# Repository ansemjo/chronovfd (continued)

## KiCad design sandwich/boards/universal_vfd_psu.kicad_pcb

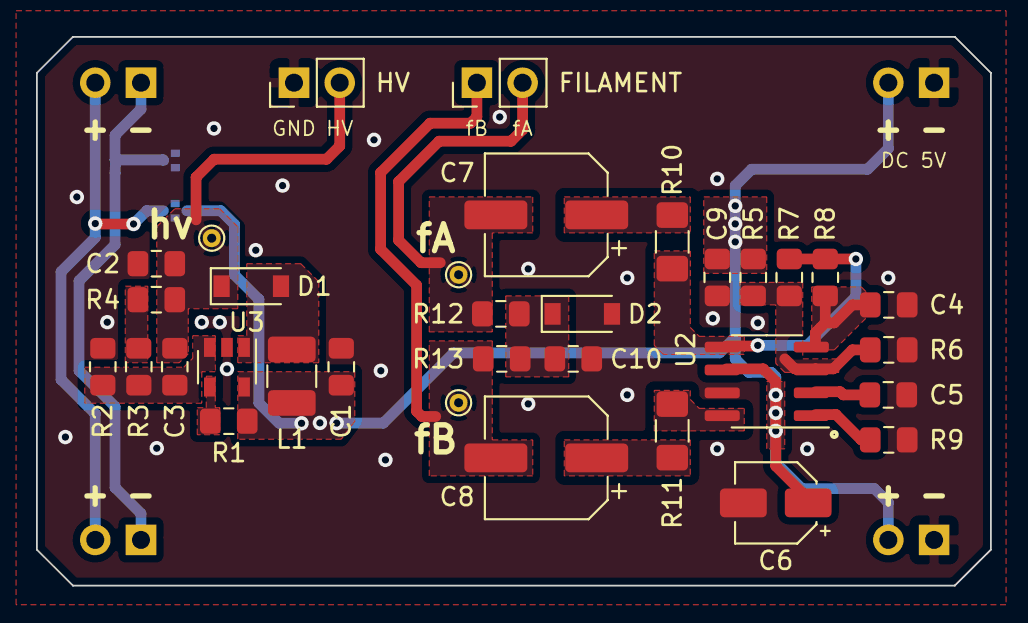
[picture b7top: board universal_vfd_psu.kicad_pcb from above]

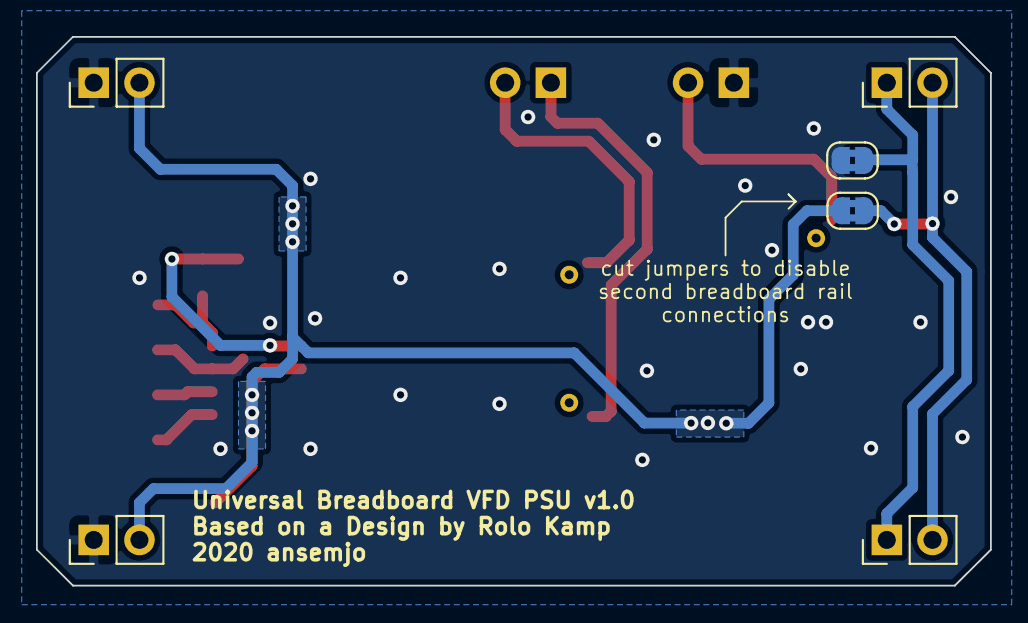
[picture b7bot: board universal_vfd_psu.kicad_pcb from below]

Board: 2 copper layers, 53.0 x 30.5 mm, 32 parts (2 on the bottom side), 18 nets.

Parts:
C1: 2.2µF; C_0805_2012Metric_Pad1.15x1.40mm_HandSolder
C2: 4.7µF; C_0805_2012Metric_Pad1.15x1.40mm_HandSolder
C3: 82pF; C_0805_2012Metric_Pad1.15x1.40mm_HandSolder
C4: 10nF; C_0805_2012Metric_Pad1.15x1.40mm_HandSolder
C5, C10: 1µF; C_0805_2012Metric_Pad1.15x1.40mm_HandSolder
C6: 10µF; CP_Elec_4x5.4
C7, C8: 47µF; CP_Elec_6.3x5.9
C9: 100nF; C_0805_2012Metric_Pad1.15x1.40mm_HandSolder
D1: 1N5819HW-7-F; D_SOD-123
D2: 3.3V; D_SOD-123
FILAMENT: PinHeader_1x02_P2.54mm_Vertical
GND: SolderJumper-2_P1.3mm_Bridged2Bar_RoundedPad1.0x1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; SolderJumper-2_P1.3mm_Bridged2Bar_RoundedPad1.0x1.5mm
HV: PinHeader_1x02_P2.54mm_Vertical
L1: 10µH; L_1210_3225Metric_Pad1.42x2.65mm_HandSolder
R1: 47kΩ; R_0805_2012Metric_Pad1.15x1.40mm_HandSolder
R2: 13kΩ; R_0805_2012Metric_Pad1.15x1.40mm_HandSolder
R3: 240kΩ; R_0805_2012Metric_Pad1.15x1.40mm_HandSolder
R4, R5, R6, R7, R9: 10kΩ; R_0805_2012Metric_Pad1.15x1.40mm_HandSolder
R8: 2.2kΩ; R_0805_2012Metric_Pad1.15x1.40mm_HandSolder
R10, R11: 10Ω; R_1206_3216Metric_Pad1.42x1.75mm_HandSolder
R12, R13: 220Ω; R_0805_2012Metric_Pad1.15x1.40mm_HandSolder
U2: LM4871MX_NOPB; SOIC-8_3.9x4.9mm_P1.27mm
U3: LM2733YMF; SOT-23-5
VCC: SolderJumper-2_P1.3mm_Bridged2Bar_RoundedPad1.0x1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; SolderJumper-2_P1.3mm_Bridged2Bar_RoundedPad1.0x1.5mm

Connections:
/5V: C1.1, C6.1, C9.1, L1.1, R1.1, R5.1, U2.6, U3.5, VCC.2
/FIL_A: C7.2, FILAMENT.2, R12.2
/FIL_B: C8.2, FILAMENT.1, R13.2
/FIL_SHDN: R9.1, U2.1
/HV: C2.1, C3.2, D1.1, HV.2, R4.1
/~HV_SHDN~: R1.2, U3.4
GND: C1.2, C2.2, C4.2, C5.2, C6.2, C9.2, C10.2, D2.2, GND.2, HV.1, R2.1, R6.2, R9.2, U2.7, U3.2
unnamed: C3.1, R2.2, R3.2, U3.3
unnamed: C4.1, R8.1, U2.4
unnamed: C5.1, U2.2
unnamed: C7.1, R10.1
unnamed: C8.1, R11.1
unnamed: C10.1, D2.1, R12.1, R13.1
unnamed: D1.2, L1.2, U3.1
unnamed: R3.1, R4.2
unnamed: R5.2, R6.1, R7.2, U2.3
unnamed: R7.1, R8.2, R10.2, U2.5
unnamed: R11.2, U2.8

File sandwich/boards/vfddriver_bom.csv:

References,Value,Quantity Per PCB,Part,Digi-Key PN,MPN,Mfg
C9,100nF,1,C_Small,1276-1099-1-ND,CL21B104KACNNNC,Samsung
C4,10nF,1,C_Small,311-1136-1-ND,CC0805KRX7R9BB103,Yageo
C6,10µF,1,CP_Small,493-2100-1-ND,UWX1C100MCL1GB,Nichicon
C5 C10,1µF,2,C_Small,1276-6469-1-ND,CL21B105KAFNNNG,Samsung
C1 C2,4.7µF,2,C_Small,587-5485-1-ND,UMK212BBJ475KG-T,Taiyo Yuden
C7 C8,47µF,2,CP_Small,493-6385-1-ND,UCD1E470MCL1GS,Nichicon
C3,82pF,1,C_Small,311-1110-1-ND,CC0805JRNPO9BN820,Yageo
D1,1N5819HW-7-F,1,1N5819,1N5819HW-FDICT-ND,1N5819HW-7-F,Diodes Inc.
D2,3.3V,1,D_Zener_Small,MMSZ4684T1GOSCT-ND,MMSZ4684T1G,ON Semi
J1,Connection Header,1,Conn_01x08_Male,S2112EC-40-ND,PREC040DBAN-M71RC,Sullins
L1,10µH,1,L_Small,587-6332-1-ND,LBC3225T100MR,Taiyo Yuden
R4 R5 R6 R7 R9,10kΩ,5,R_Small,311-10.0KCRCT-ND,RC0805FR-0710KL,Yageo
R10 R11,12Ω 0.25W,2,R_Small,311-10.0FRCT-ND,RC1206FR-0710RL,Yageo
R2,13kΩ,1,R_Small,311-13.0KCRCT-ND,RC0805FR-0713KL,Yageo
R8,2.2kΩ,1,R_Small,311-2.20KCRCT-ND,RC0805FR-072K2L,Yageo
R12 R13,220Ω,2,R_Small,311-220CRCT-ND,RC0805FR-07220RL,Yageo
R3,240kΩ,1,R_Small,311-240KCRCT-ND,RC0805FR-07240KL,Yageo
R1 R14,47kΩ,2,R_Small,311-47.0KCRCT-ND,RC0805FR-0747KL,Yageo
U4,HV5812WG,1,HV5812WG,HV5812WG-GCT-ND,HV5812WG-G,Microchip
U1,IVL2-5_7,1,IVL2-5_7,,IVL2-7/5,
U3,LM2733YMF,1,LM2733YMF,LM2733YMF/NOPBCT-ND,LM2733YMF/NOPB,Texas Instr
U2,LM4871MX_NOPB,1,LM4871MX_NOPB,LM4871MX/NOPBCT-ND,LM4871MX/NOPB,Texas Instr

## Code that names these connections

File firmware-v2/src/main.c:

#include <avr/io.h>
#include <avr/interrupt.h>
#include <util/delay.h>
#include <assert.h>

#include "segments.h"
#include "i2c_peripheral.h"

// filament pins
#define filFWD  PIN2_bm // PB2
#define filREV  PIN3_bm // PB3
#define filVREF PIN6_bm // PA6

// hv5812 pins
#define hvDATA   PIN1_bm // PA1
#define hvCLOCK  PIN3_bm // PA3
#define hvSTROBE PIN4_bm // PA4

// setup the main cpu clock control to run at full speed
void init_cpufrequency() {
  //! check that fuse 0x02 OSCCFG has set FREQSEL = 0x02 to run at 20MHz
  assert((0b11 & FUSE_OSCCFG) == FREQSEL_20MHZ_gc);
  assert(F_CPU == 20000000L);
  _PROTECTED_WRITE(CLKCTRL.MCLKCTRLA, CLKCTRL_CLKSEL_OSC20M_gc); // select internal oscillator
  _PROTECTED_WRITE(CLKCTRL.MCLKCTRLB, (0 << CLKCTRL_PEN_bp));    // disable prescaler for full 20 MHz
}

// setup output pins to filament driver
void init_filament(uint8_t dac_data) {
  // setup output pins
  PORTA.DIRSET = filVREF;         // setup vref pin as output
  PORTA.OUTCLR = filVREF;         // start with reference voltage low
  PORTB.DIRSET = filFWD | filREV; // setup direction pins as outputs
  PORTB.OUTSET = filFWD;          // set one direction pin high
  // setup dac for vref pin
  DAC0.DATA  = dac_data;                           // write specified value
  register8_t vref = (VREF.CTRLA & ~(0b00000111)); // read & mask the current ctrla setting
  VREF.CTRLA = vref | VREF_DAC0REFSEL_2V5_gc;      // select internal 2.5 V voltage reference for dac
  DAC0.CTRLA = DAC_ENABLE_bm | DAC_OUTEN_bm;       // enable dac and output to PA6
}

// send data to the shift register and latch to vfd outputs
void display(uint16_t data) {
  PORTA.OUTCLR = hvSTROBE;
  while (!(SPI0.INTFLAGS & SPI_DREIF_bm)) { ; }
  SPI0.DATA = 0xFF & (data >> 8);
  while (!(SPI0.INTFLAGS & SPI_DREIF_bm)) { ; }
  SPI0.DATA = 0xFF & (data);
  while (!(SPI0.INTFLAGS & SPI_TXCIF_bm)) { ; }
  SPI0.INTFLAGS |= SPI_TXCIF_bm;
  PORTA.OUTSET = hvSTROBE;
  asm volatile("nop");
  PORTA.OUTCLR = hvSTROBE;
}

// setup spi controller to communicate with hv5812 shift register
void init_hv5812() {
  PORTA.DIRSET = hvDATA | hvCLOCK | hvSTROBE;  // setup pins to hv5812 as outputs
  PORTA.OUTCLR = hvDATA | hvCLOCK | hvSTROBE;  // set all pins low explicitly
  SPI0.CTRLA  = SPI_PRESC_DIV4_gc;             // set spi prescaler to result in ca. 5 MHz clock
  SPI0.CTRLA |= SPI_MASTER_bm | SPI_ENABLE_bm; // enable spi in controller mode
  SPI0.CTRLB  = SPI_BUFEN_bm | SPI_SSD_bm;     // double-buffered mode, don't use chip select
  display(0);                                  // all segments and grids off initially
}


volatile int digit = 0;
uint16_t digits[] = {
  G1 | Aa|Ad|Ae|Af|Ag, // E
  G2 | Ab|Ac|Ae|Af|Ag, // H
  G4 | Ad|Ae|Af, // L
  G5 | Aa|Ab|Ac|Ad|Ae|Af, // O
};
#define DIGITS (sizeof(digits)/sizeof(uint16_t))

// periodic interrupt service routing for digit time-multiplexing
ISR(RTC_PIT_vect) {
  RTC.PITINTFLAGS = RTC_PI_bm;    // clear interrupt flag
  display(digits[digit]);         // display next digit
  digit = (digit+1) % DIGITS;     // increment digit position
  PORTB.OUTTGL = filFWD | filREV; // toggle filament drive direction // TODO
}

// setup the periodic interrupt timer for digit time-multiplexing
void init_digit_multiplexing() {
  RTC.CLKSEL = RTC_CLKSEL_INT32K_gc;                 // use internal 32kHz
  RTC.PITINTCTRL = RTC_PI_bm;                        // enable periodic interrupt
  RTC.PITCTRLA = RTC_PERIOD_CYC32_gc | RTC_PITEN_bm; // enable PIT with 1 msec period
  sei();
}

// setup the adc to measure the photodiode current, i.e. ambient brightness
void init_photodiode_adc() {
  PORTA.DIRCLR = PIN7_bm;                                 // PA7 input
  PORTA.PIN7CTRL = PORT_ISC_INPUT_DISABLE_gc;             // disable input buffer
  register8_t vref = (VREF.CTRLA & ~(0b01110000));        // read & mask the current ctrla setting
  VREF.CTRLA = vref | VREF_ADC0REFSEL_0V55_gc;            // select internal 0.55 V voltage reference for adc
  ADC0.CTRLC = ADC_REFSEL_INTREF_gc | ADC_PRESC_DIV64_gc  // compate with internal reference, /64 prescaler
    | ADC_SAMPCAP_bm;                                     // use the smaller sampling capacitance
  ADC0.CTRLD = ADC_INITDLY_DLY32_gc | ADC_ASDV_ASVON_gc;  // some sample delay and randomization
  ADC0.SAMPCTRL = 0x1F;                                   // longer sampling time for high-impedance input
  ADC0.MUXPOS = ADC_MUXPOS_AIN7_gc;                       // sample on PA7 input
  ADC0.CTRLA |= ADC_ENABLE_bm;                            // enable
  ADC0.COMMAND = ADC_STCONV_bm;                           // start first conversion right away
}

// simple moving average over last few measurements
uint16_t samples[] = { 0, 0, 0, 0, 0, 0, 0, 0, 0, 0, 0, 0, 0, 0, 0, 0 };
unsigned idx = 0;
unsigned sum = 0;
#define SAMPLES (sizeof(samples)/sizeof(samples[0]))

// sample the photodiode adc and return averaged value
uint16_t measure_photodiode() {
  ADC0.COMMAND = ADC_STCONV_bm; // start conversion
  while (ADC0.COMMAND & ADC_STCONV_bm); // wait
  uint16_t sample = ADC0.RES;
  sum -= samples[idx];
  samples[idx] = sample;
  sum += samples[idx];
  idx = (idx+1) % SAMPLES;
  return sum / SAMPLES;
}

// infinite loop with random noise
void noise() {
  const int delay = 30;
  while (1) {
    digits[0] = G1 | (SEGMENTMASK & rand());
    digits[1] = G2 | (SEGMENTMASK & rand());
    digits[2] = G4 | (SEGMENTMASK & rand());
    digits[3] = G5 | (SEGMENTMASK & rand());
    _delay_ms(delay);
  }
}

// continiously sample the ambient brightness and display the value
void adcdisplay() {
  init_photodiode_adc();
  const uint16_t masks[] = { G1, G2, G4, G5 };
  uint16_t measure;
  while (1) {
    measure = measure_photodiode();
    digits[0] = masks[0] | segment_lookup((measure/1000) % 10);
    digits[1] = masks[1] | segment_lookup((measure/100 ) % 10);
    digits[2] = masks[2] | segment_lookup((measure/10  ) % 10);
    digits[3] = masks[3] | segment_lookup((measure/1   ) % 10);
    _delay_ms(100);
  }
}

volatile uint8_t i2c_data[4] = { 0, 0, 0, 0 };

// setup as i2c peripheral
init_i2c_peripheral() {

  i2c_peripheral_init(0x68);
  sei();

  while (1) {
    digits[0] = G1 | segment_lookup(i2c_data[0]);
    digits[1] = G2 | segment_lookup(i2c_data[1]);
    digits[2] = G4 | segment_lookup(i2c_data[2]);
    digits[3] = G5 | segment_lookup(i2c_data[3]);
    _delay_ms(100);
  }

}

/* i2c wishlist:
 * (https://github.com/sparkfun/Serial7SegmentDisplay/wiki/Special-Commands#decimal)
 *   clear display
 *   colon on/off (cursor control)
 *   begin every write left and then loop aroung with every fourth byte
 *   brightness control
 *   set specific digit
 *   raw data entry escape
 *   address config
 *   factory reset ?!
 *   store configuration in eeprom
 */

void main(void) {

  init_cpufrequency();
  init_filament(200);
  init_hv5812();
  init_digit_multiplexing();

  // show EHLO at beginning
  digits[0] = G1 | segment_lookup('E');
  digits[1] = G2 | segment_lookup('H');
  digits[2] = G4 | segment_lookup('L');
  digits[3] = G5 | segment_lookup('O');
  _delay_ms(600);

  // noise();
  //adcdisplay();
  init_i2c_peripheral();

}

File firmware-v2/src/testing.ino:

#define FIL_FWD 5
#define FIL_REV 4
#define FIL_REF 2

#define HV_DATA   8
#define HV_CLOCK  10
#define HV_STROBE 0

void initpin(int pin, int state) {
  pinMode(pin, OUTPUT);
  digitalWrite(pin, state);
}

void toggle(int pin) {
  digitalWrite(pin, !digitalRead(pin));
}

void setup() {

  // setup pins for filament driver
  initpin(FIL_FWD, LOW);  // forward
  initpin(FIL_REV, HIGH);  // reverse
  initpin(FIL_REF, LOW); // reference

  // turn on filament
  VREF.CTRLA = 0x03; // set reference voltage to 4.3V
  analogWrite(FIL_REF, 100);

  // setup hv pins
  initpin(HV_DATA, LOW);
  initpin(HV_CLOCK, LOW);
  initpin(HV_STROBE, LOW);

  delay(100);

  // turn on all segments
  digitalWrite(HV_STROBE, LOW);
  shiftOut(HV_DATA, HV_CLOCK, MSBFIRST, 0xff);
  shiftOut(HV_DATA, HV_CLOCK, MSBFIRST, 0xff);
  digitalWrite(HV_STROBE, HIGH);

  delay(1000);

}

#define SEGMENTS 0x1dda
#define Aa 0x0c12
#define An 0x0c02
#define At 0x0c90
#define G1 0x2000
#define G2 0x0001
#define G3 0x0004
#define G4 0x0020
#define G5 0x0200

void filwait() {
  for (int i = 0; i < 3; i++) {
    toggle(FIL_FWD);
    toggle(FIL_REV);
    delay(1);
  }
}

void out(uint16_t data) {
  digitalWrite(HV_STROBE, LOW);
  shiftOut(HV_DATA, HV_CLOCK, MSBFIRST, 0xff & (data >> 8));
  shiftOut(HV_DATA, HV_CLOCK, MSBFIRST, 0xff & (data >> 0));
  digitalWrite(HV_STROBE, HIGH);
}

void loop() {

  filwait();
  out(Aa | G1);
  filwait();
  out(An | G2);
  filwait();
  out(At | G4);
  filwait();
  out(An | G5);

}

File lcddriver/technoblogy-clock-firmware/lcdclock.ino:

/* Low-Power LCD Clock

   David Johnson-Davies - www.technoblogy.com - 4th May 2021
   AVR128DA48 @ 24 MHz (internal oscillator; BOD disabled)
   
   CC BY 4.0
   Licensed under a Creative Commons Attribution 4.0 International license: 
   http://creativecommons.org/licenses/by/4.0/
*/

#include <avr/io.h>
#include <avr/interrupt.h>
#include <avr/sleep.h>

// Seven segment definitions

const int CharLen = 15;
uint8_t Char[CharLen] = {
//  abcdefg  Segments
  0b1111110, // 0
  0b0110000, // 1
  0b1101101, // 2
  0b1111001, // 3
  0b0110011, // 4
  0b1011011, // 5
  0b1011111, // 6
  0b1110000, // 7
  0b1111111, // 8
  0b1111011, // 9
  0b0000000, // 10  Space
  0b0000001, // 11  '-'
  0b1100011, // 12  Degree
  0b1001110, // 13  'C'
  0b0111110  // 14  'V'
};

const int Space = 10;
const int Minus = 11;
const int Degree = 12;
const int Celsius = 13;
const int Vee = 14;

// Ports **********************************************

PORT_t *Digit[4] = { &PORTD, &PORTC, &PORTA, &PORTB };

void PortSetup () {
  for (int p=0; p<4; p++) Digit[p]->DIR = 0xFF;       // All pins outputs
  PORTE.DIR = PIN0_bm;                      // COMs outputs, PE0 and PE1
  PORTF.DIR = PIN5_bm | PIN4_bm;                      // 1A, colon
}

// Real-Time Clock **********************************************

void RTCSetup () {
  uint8_t temp;
  // Initialize 32.768kHz Oscillator:

  // Disable oscillator:
  temp = CLKCTRL.XOSC32KCTRLA & ~CLKCTRL_ENABLE_bm;

  // Enable writing to protected register
  CPU_CCP = CCP_IOREG_gc;
  CLKCTRL.XOSC32KCTRLA = temp;

  while (CLKCTRL.MCLKSTATUS & CLKCTRL_XOSC32KS_bm);   // Wait until XOSC32KS is 0
  
  temp = CLKCTRL.XOSC32KCTRLA | CLKCTRL_LPMODE_bm;      // Use External Crystal & low power
  
  // Enable writing to protected register
  CPU_CCP = CCP_IOREG_gc;
  CLKCTRL.XOSC32KCTRLA = temp;
  
  temp = CLKCTRL.XOSC32KCTRLA | CLKCTRL_ENABLE_bm;    // Enable oscillator
  
  // Enable writing to protected register
  CPU_CCP = CCP_IOREG_gc;
  CLKCTRL.XOSC32KCTRLA = temp;
  
  // Initialize RTC
  while (RTC.STATUS > 0);                             // Wait until registers synchronized

  // 32.768kHz External Crystal Oscillator (XOSC32K)
  RTC.CLKSEL = RTC_CLKSEL_XOSC32K_gc;

  RTC.PITINTCTRL = RTC_PI_bm;                         // Periodic Interrupt: enabled
  
  // RTC Clock Cycles 512, enabled ie 64Hz interrupt
  RTC.PITCTRLA = RTC_PERIOD_CYC512_gc | RTC_PITEN_bm;
}

// Display Time **********************************************

void DisplayTime (unsigned long halfsecs) {
  uint8_t minutes = (halfsecs / 120) % 60;
  #ifdef TWELVEHOUR
  uint8_t hours = (halfsecs / 7200) % 12 + 1;
  #else
  uint8_t hours = (halfsecs / 7200) % 24;
  #endif
  Digit[0]->OUT = Char[hours/10];
  Digit[1]->OUT = Char[hours%10];
  Digit[2]->OUT = Char[minutes/10];
  uint8_t units = Char[minutes%10];
  Digit[3]->OUT = units;
  uint8_t colon = ((halfsecs >> 1) & 1)<<4;                  // Toggle colon at 1Hz   
  PORTF.OUT = (units>>1 & PIN5_bm) | colon;
}

// Interrupt Service Routine at 64Hz
ISR(RTC_PIT_vect) {
  static uint8_t cycles = 0;
  static unsigned long halfsecs;
  RTC.PITINTFLAGS = RTC_PI_bm;                        // Clear interrupt flag
  // Toggle segments
  for (int p=0; p<4; p++) Digit[p]->OUTTGL = 0xFF;    // Toggle all PORTA,B,C,D pins
  PORTE.OUTTGL = PIN0_bm;                   // Toggle COMs, PE0 and PE1
  PORTF.OUTTGL = PIN5_bm | PIN4_bm;                   // Toggle segment 1A, Colon

  cycles++;
  if (cycles < 32) return;
  cycles = 0;

  // Update time
  halfsecs = (halfsecs+1) % 172800;                   // 24 hours
                 
  if (MinsButton()) halfsecs = ((halfsecs/7200)*60 + (halfsecs/120 + 1)%60)*120;
  if (HoursButton()) halfsecs = halfsecs + 7200;

  DisplayTime(halfsecs);
}

// Buttons **********************************************

void ButtonSetup () {
  PORTE.PIN3CTRL = PORT_PULLUPEN_bm;                  // PE3 input pullup
  PORTE.PIN2CTRL = PORT_PULLUPEN_bm;                  // PE2 input pullup
}

boolean MinsButton () {
  return (PORTE.IN & PIN2_bm) == 0;                   // True if button pressed
}

boolean HoursButton () {
  return (PORTE.IN & PIN3_bm) == 0;                   // True if button pressed
}

// Sleep **********************************************

void SleepSetup () {
  SLPCTRL.CTRLA |= SLPCTRL_SMODE_PDOWN_gc;
  SLPCTRL.CTRLA |= SLPCTRL_SEN_bm;
}

// Setup **********************************************

void setup () {
  PortSetup();
  ButtonSetup();
  SleepSetup();
  RTCSetup();
}

// Just stay asleep to save power unless woken by an interrupt
void loop () {
  sleep_cpu();
}

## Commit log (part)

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2020-03-02 working clock example with ds3231 on i2c
2020-03-02 attempt to detect connected i2c master through scl level
2020-03-04 rewrite for finished protoboard clock
2020-03-04 move firmware project to subdirectory
2020-03-05 move segments and char lookup to separate header
2020-03-05 split hv5812p bitbanging into HV class
2020-03-05 attempt to use background refresh with timer interrupts and manual rtc communication
2020-03-05 improve display refresh timer, move display buffer to hv class
2020-03-06 rollover animation on changed digits
2020-04-01 fix a bug in segments lookup
2020-04-01 reduce brightness correction that was due to floaty blanking pin
2020-04-01 add aux script to set rtc date via pi2co dongle
2020-04-01 fix a bug in i2c clock script: hexdump squeezing
2020-04-01 rewrite as a pure i2c slave display with demo clock script
2020-07-17 play with a few i2ctransfer scripts
2020-07-23 begin tracking my kicad feng-shui
    pretty nice power supply submodule layouts so far ..
2020-07-23 further psu layout optimizations
2020-07-24 commit the board version that went to aisler, more silkscreen info
2020-07-24 forgot to include a gitignore
2020-07-24 rename kicad project files for driver board
2020-07-24 create a breadboard psu layout from universal psu modules
2020-07-26 begin tracking work on clock shield with esp32
2020-07-28 finished schematic for clockcore, pcb layout todo
2020-07-29 finished pcb routing for clockcore, forgot to add zener
2020-07-30 final clockcore design v2_copy ... i think
2020-07-31 update vfddriver resistor values, 10 ohm is too dark, 4.7 too bright
2020-07-31 add breadboard experiment python scripts
2020-07-31 add research notes about vfds in general
2020-07-31 add universal vfd psu design files by rolo kamp
2020-07-31 modify firmware to run display tests from arduino uno
2020-07-31 add readme and some images for github
2020-08-02 add ds18b20 to clock core and reroute a few traces
2020-08-02 updated crystal in schematic so pin3 is gnd, added teardrops
2020-08-07 add digikey bom for clockcore
2020-08-07 populate part numbers in clockcore symbol fields, generate new bom with kibom
2020-08-09 brightness correction for hendriks vfd
2020-08-13 stupid simple full-on firmware to light up all segments
2020-08-13 implement all segments on with esp-idf and hardware spi
2020-08-14 copy and tweak old segment mapping, background timer blinking
2020-08-15 add clockcore schematic pdf
2020-08-15 move vfd spi driver to seperate files
2020-08-17 functioning multiplexing with esp_timer api
2020-08-17 refactor to use handle on heap, experiment with filament dimming
2020-08-19 hardware: add usb-c receptacle 3d model
    copied from esden/Glasgow @ dcf681eff68b47ce297b1218d60e69f61a113a32
2020-08-19 hardware: add switches 3d model and configure D1 F1 with similar 1206 models
2020-08-20 hardware: generate interactive bom html
2020-08-20 firmware: implement ambient light aware dimming with photodiode
2020-08-20 hardware: add page setting for rev 1.0 before photodiode changes
2020-08-20 hardware: tidy up, fix photodiode, (re)export (i)boms and schematics
2020-08-20 hardware: add new pcb renders
2020-08-21 readme
2020-08-24 hardware: add erratum on how to fix the photodiode on rev1.0 boards
2020-08-25 firmware: put ambient light dimmer in seperate file
2020-08-25 firmware: attempt using esp-idf-lib to talk to rtc
2020-08-25 firmware: modify local copy of ds1307 library to remove semaphores
2020-08-26 readme: add an updated picture of the assembled clock
2020-08-26 firmware: simplify ambient light mapper function
2020-08-26 firmware: add and fix ds1307.c rtc config checks, use rtc as external clock source
2020-08-27 miscellaneous
2020-09-03 firmware: switch digitmux to hwtimer with semaphore-blocked task
2020-09-03 fw: move i2c init and clockface task to seperate files
2020-09-04 fw: add wifi provisioning and sntp sync demo
2020-09-04 fw: add custom board definition for clockcore with ESP32-WROOM-32E(8MB)
2020-09-04 fw: use pragma once, refactor rtc for global handle, seperate animations files
2020-09-04 fw: refactoring; vfd and mux changed to global variables
2020-09-04 fw: add new fader animations
2020-09-05 fw: hacked together blocking behaviour on missing provisioning on boot
2020-09-06 fw: much simpler wifi provisioning just using defaults
2020-09-06 fw: explicitly zero out hv5812 outputs and display buf on init
2020-09-06 fw: store lastsync date in rtc ram for conditional resync
2020-09-07 fw: replace a few taskdelays with taskdelayuntil where periodic is needed
2020-09-07 fw: improve vfddriver digitmux to reduce flicker with active event loop
2020-09-07 fw: tidy up wirelss functions, use event group for connection status bits
2020-09-07 fw: better resync logic, daily schedule
2020-09-07 fw: implement simple factory reset on gpio0
2020-09-24 fw: update and fix espidf @ 4.1, add textrunner animation
2020-09-24 tidy up readme and add license
2020-09-24 add more pictures of assembled boards
2020-09-25 add linguist rules to exclude generated bom files from statistics
2020-10-09 add scan of my protoboard clock layout sketch
2021-02-23 revived my protoclock, added tidied-up dual firmware directory from old commit
2021-03-14 fw: pin requirements for platformio in a virtualenv
2021-03-14 fw: add code to check if my display has burn-in
2021-08-27 hw: tweaked pin spacing in ivl2-7/5 footprint
2021-08-27 hw: [WIP] add attiny412, remove traces in prep for v2
2021-08-28 hw: tweak universal psu to test new filament driver
2021-08-28 fw: commit old changes to filament dimmer code
2021-08-28 hw: finished h-bridge psu test board
2021-08-28 hw: tweak breadboard psu for fabrication
2021-12-20 fw: fix build, pin new toolchain versions
2022-01-11 remove error in readme
2022-01-11 fw: add github workflow to test compilation
2022-01-14 hw: update h-bridge psu with experiences as text on schematic
2022-01-14 hw: update breadboard hbridge psu to kicad 6
2022-01-14 hw: [WIP] migrate libraries, put everything in subdirectories
2022-01-14 hw: [WIP] begin rework vfddriver with hbridge filament
2022-01-16 hw: add more footprints from updiprog
2022-01-16 hw: finished redesign of vfddriver frontplate
2022-02-08 fw: first simple arduino sketch to test vfddriver v2
2022-02-09 fw: rewrite sketch in baremetal avrxmega3 code, copied segments.h
2022-02-10 hw: saved interactive bom that i used for soldering
2022-02-10 fw: add requirements.txt with dev tools
2022-02-10 fw: implement digit multiplexing with RTC PIT, demo with random noise
2022-02-11 fw: implement ambient brightness measurement with photodiode
2022-09-01 fw: add i2c_peripheral with a simple four-byte data array
2022-09-01 doc: add a link to nick poole's vfd driver
2022-09-01 hw: begin new lcd clock face, not routed yet
2022-09-02 hw: finished routing lcd clock face
2022-09-22 added subdirectory with low-power lcd clock firmware
2022-10-04 remove bidirectional escape char
2024-05-23 add eval board for Si4706 based RDS receiver
2024-10-19 lcddriver: add inverted variant of the firmware
2024-10-19 chronocase: 3d-printable cases
2026-01-12 move case designs to /enclosure
2026-01-12 fw: improved i2c peripheral to set brightness and remove photodiode code
2026-01-12 fw: add circuitpython examples for firmware-v2
2026-01-12 protoclock: move photo and wiring sketch into directory
2026-01-13 radio: small pcb update, add example firmware to get RDS signal
2026-01-25 reorganization; resurface original vfddriver v1 design and put in sandwich/; new rust firmware
2026-01-26 remove github workflow
2026-01-26 update attributes with generated files for language stats
2026-01-27 add more photos, update main README
2026-01-31 vfddriver: new renders, add 3d model for vfd tube
    The 3D model was made by Patrick Kübler, copied from https://github.com/Pakue95/VFD_Watch/
2026-01-31 update main and add deedicated vfddriver readme
2026-01-31 replace firmware with rust and finish readme
2026-01-31 quickmenu jumps to directories
2026-01-31 si4706: add latest rds test firmware and another pdf with good info
2026-02-03 radiocore: redesign the Si4706 experiment to a new clock controller with ESP32-C3 and RTC
2026-02-15 vfddriver: change i2c addr to 0x42
    the DS1338Z RTC also uses 0x68, so there'd be a collision by default
2026-02-15 radiocore: add ibom for assembly, found pcb errata and test firmware
2026-02-15 radiocore: move firmware to other circuitpython files
2026-03-22 radiocore: initial rust firmware with embassy + esp_hal
    essential parts are wired up; time updates for display come directly from RDS for now but with good FM signal this is already a viable clock
2026-03-24 radiocore: show date from rtc and store rds updates
2026-03-27 radiocore: add nightlight dimmer based on approximated sunset time
2026-03-29 radiocore: reset the chip on panics
    if ESP_BACKTRACE=RESET during compile
2026-04-02 radiocore: remove manual datetime check and just let jiff panic
2026-04-02 radiocore: check rds updates for plausibility using drift and majority vote
2026-04-06 radiocore: add bounds check in rds_to_julian to avoid subtraction underflow
2026-04-07 radiocore: be more verbose on serial to debug rejection of bad rds reception
2026-04-23 build(deps): bump rand from 0.8.5 to 0.8.6 in /vfddriver/firmware
    Bumps [rand](https://github.com/rust-random/rand) from 0.8.5 to 0.8.6.
    - [Release notes](https://github.com/rust-random/rand/releases)
    - [Changelog](https://github.com/rust-random/rand/blob/0.8.6/CHANGELOG.md)
    - [Commits](https://github.com/rust-random/rand/compare/0.8.5...0.8.6)
    ---
    updated-dependencies:
